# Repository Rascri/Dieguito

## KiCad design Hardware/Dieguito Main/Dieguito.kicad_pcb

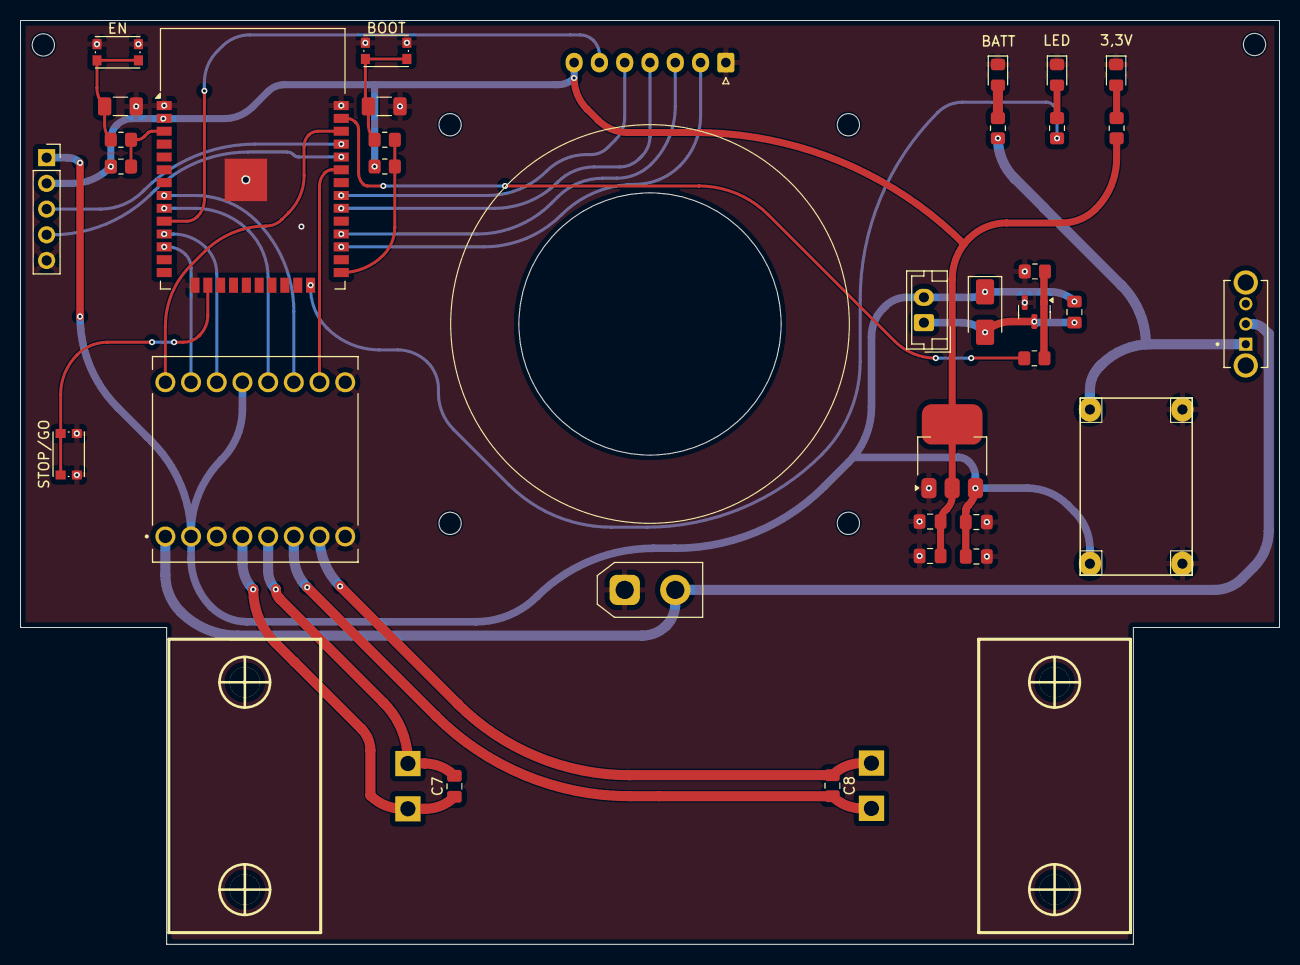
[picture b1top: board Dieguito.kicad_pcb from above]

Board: 2 copper layers, 124.4 x 91.3 mm, 41 parts (1 on the bottom side), 34 nets.

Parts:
3,3V: POWER; LED_0805_2012Metric_Pad1.15x1.40mm_HandSolder
BATT: POWER; LED_0805_2012Metric_Pad1.15x1.40mm_HandSolder
BOOT: BOOT; SW_Push_1P1T_NO_CK_KMR2
Bracket1, Bracket2: VAL**; Pololu_Micro_Bracket_Wheel_42mm
C1, C4, C7, C8: 100n; C_0805_2012Metric_Pad1.18x1.45mm_HandSolder
C2, C3: 10u; C_0805_2012Metric_Pad1.18x1.45mm_HandSolder
C5, C6: 1n; C_1206_3216Metric_Pad1.33x1.80mm_HandSolder
C9: 0.1uF; C_0805_2012Metric_Pad1.18x1.45mm_HandSolder
D4: SS34; D_SMA
EN: ENABLE; SW_Push_1P1T_NO_CK_KMR2
H1, H2: Mounting_Hole; MountingHole_2.2mm_M2
J1: XT30; AMASS_XT30UPB-M_1x02_P5.0mm_Vertical
J2, J3: Cable_PAD; Cable_3_1,5mm
J4: Programador; PinSocket_1x05_P2.54mm_Vertical
J5: Sensores; JST_XH_S7B-XH-A-1_1x07_P2.50mm_Horizontal
J6: Turbina; JST_EH_B2B-EH-A_1x02_P2.50mm_Vertical
LED: POWER; LED_0805_2012Metric_Pad1.15x1.40mm_HandSolder
Q1: AO3400A; SOT-23
R1, R3, R5: 470; R_0805_2012Metric_Pad1.20x1.40mm_HandSolder
R2, R7: 1k; R_0805_2012Metric_Pad1.20x1.40mm_HandSolder
R4, R6: 10k; R_0805_2012Metric_Pad1.20x1.40mm_HandSolder
R8: 47k; R_0805_2012Metric_Pad1.20x1.40mm_HandSolder
R9: 100; R_0805_2012Metric_Pad1.20x1.40mm_HandSolder
STOP/GO: GO/STOP; SW_Push_1P1T_NO_CK_KMR2
SW4: SW_SPDT; SW_EG1247
U1: ROB-14450; MODULE_ROB-14450
U2: ESP32-WROOM-32
U3: AMS1117-3.3; SOT-223-3_TabPin2
U4: Mini360; Mini360_step-down

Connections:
+3.3V: C3.1, C4.1, J4.2, J5.7, R2.1, R4.2, R6.2, U2.2 (VDD), U3.2 (VO)
+5V: C1.1, C2.1, C9.1, D4.1 (K), J4.1, J6.2, U1.2 (VCC), U1.13 (STBY), U3.3 (VI), U4.3 (OUT)
/VM: J1.2, SW4.2 (B), U1.1 (VM)
AI1: U1.14 (AI1), U2.11 (IO26)
AI2: U1.15 (AI2), U2.12 (IO27)
BI1: U1.12 (BI1), U2.9 (IO33)
BI2: U1.11 (BI2), U2.8 (IO32)
D13: STOP/GO.1, U2.16 (IO13)
D23: R9.2, U2.37 (IO23)
EN: R3.2, R4.1, U2.3 (EN)
GND: 3,3V.1 (K), BATT.1 (K), BOOT.1, C1.2, C2.2, C3.2, C4.2, C5.1, C6.1, EN.1, J1.1, J4.5, J5.1, LED.1 (K), Q1.2 (S), R8.1, STOP/GO.2, U1.3 (GND), U1.8 (GND), U1.9 (GND), U2.1 (GND), U2.15 (GND), U2.38 (GND), U2.39 (GND), U3.1 (GND), U4.2 (GND)
IO0: R5.2, R6.1, U2.25 (IO0)
LED: R1.1, U2.24 (IO2)
M0: J5.5, U2.31 (IO19)
M1: J5.4, U2.30 (IO18)
M2: J5.3, U2.28 (IO17)
M3: J5.2, U2.27 (IO16)
unnamed: C5.2, EN.2, R3.1
unnamed: BOOT.2, C6.2, R5.1
unnamed: LED.2 (A), R1.2
unnamed: 3,3V.2 (A), R2.2
unnamed: BATT.2 (A), R7.2
unnamed: C9.2, D4.2 (A), J6.1, Q1.3 (D)
unnamed: Q1.1 (G), R8.2, R9.1
unnamed: C7.1, J2.2, U1.4 (A01)
unnamed: C7.2, J2.1, U1.5 (A02)
unnamed: C8.1, J3.2, U1.7 (B01)
unnamed: C8.2, J3.1, U1.6 (B02)
PWMA: U1.16 (PWMA), U2.36 (IO22)
PWMB: U1.10 (PWMB), U2.33 (IO21)
RXD0: J4.4, U2.34 (RXD0/IO3)
SIG: J5.6, U2.10 (IO25)
TXD0: J4.3, U2.35 (TXD0/IO1)
VCC: R7.1, SW4.1 (A), U4.1 (IN)

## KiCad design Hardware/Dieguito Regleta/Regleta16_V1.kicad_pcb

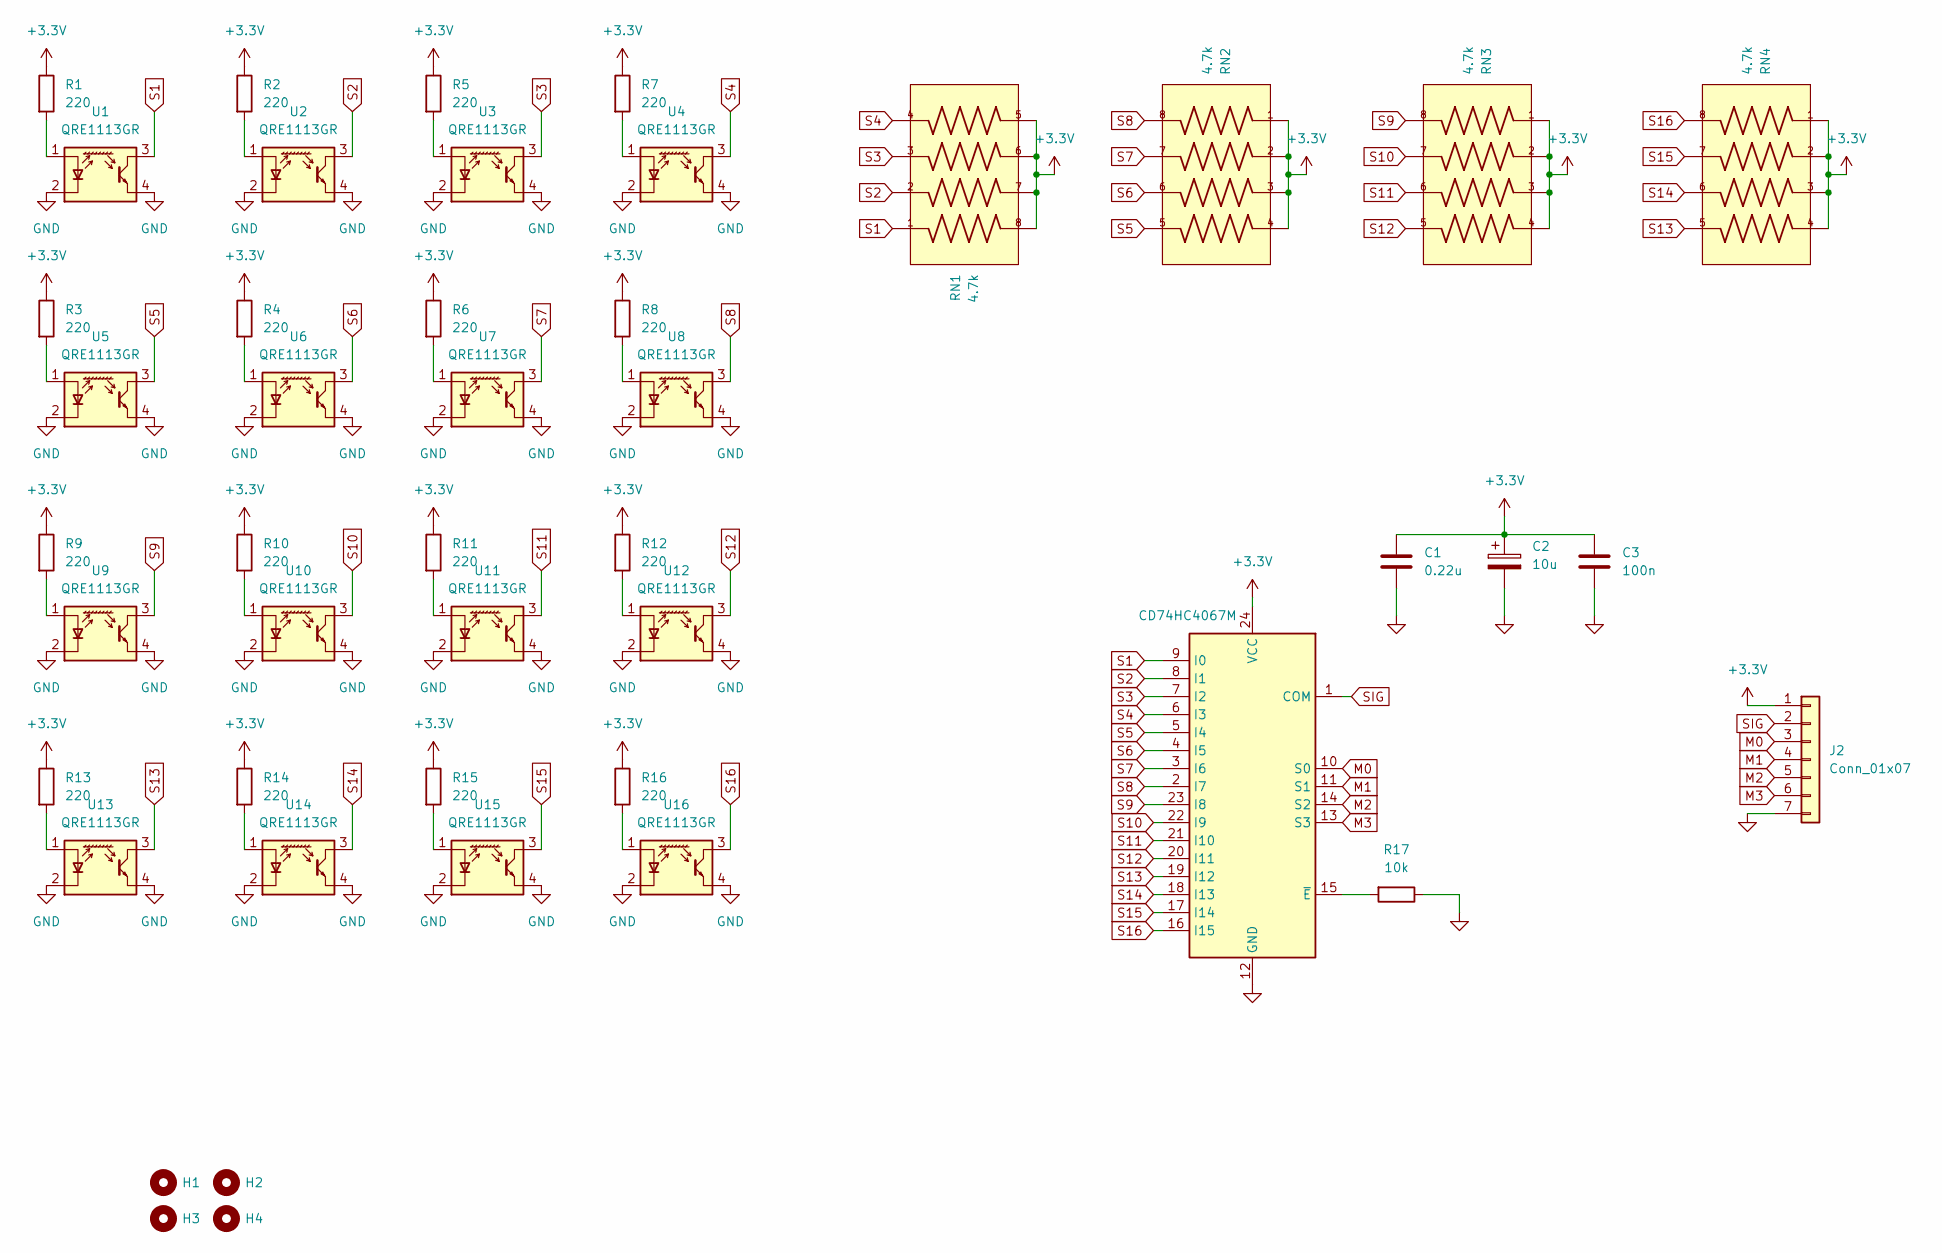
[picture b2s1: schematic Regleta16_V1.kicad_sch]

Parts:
C1: 0.22u; C_0805_2012Metric_Pad1.18x1.45mm_HandSolder
C2: 10u; CP_Elec_4x5.4
C3: 100n; C_0805_2012Metric_Pad1.18x1.45mm_HandSolder
H1, H2, H3, H4: Mounting_Hole; MountingHole_2.2mm_M2
J2: Conn_01x07; JST_XH_S7B-XH-A-1_1x07_P2.50mm_Horizontal
R1, R2, R3, R4, R5, R6, R7, R8, R9, R10, R11, R12, R13, R14, R15, R16: 220; R_0805_2012Metric_Pad1.20x1.40mm_HandSolder
R17: 10k; R_0805_2012Metric_Pad1.20x1.40mm_HandSolder
RN1, RN2, RN3, RN4: 4.7k; R_Array_Convex_4x1206
U1, U2, U3, U4, U5, U6, U7, U8, U9, U10, U11, U12, U13, U14, U15, U16: QRE1113GR; Qre1113_smd_dieguito
U18: CD74HC4067M; SOIC-24W_7.5x15.4mm_P1.27mm

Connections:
+3.3V: C1.1, C2.1, C3.1, J2.1, R1.1, R2.1, R3.1, R4.1, R5.1, R6.1, R7.1, R8.1, R9.1, R10.1, R11.1, R12.1, R13.1, R14.1, R15.1, R16.1, RN1.5, RN1.6, RN1.7, RN1.8, RN2.1, RN2.2, RN2.3, RN2.4, RN3.1, RN3.2, RN3.3, RN3.4, RN4.1, RN4.2, RN4.3, RN4.4, U18.24 (VCC)
GND: C1.2, C2.2, C3.2, J2.7, R17.1, U1.2 (K), U1.4, U2.2 (K), U2.4, U3.2 (K), U3.4, U4.2 (K), U4.4, U5.2 (K), U5.4, U6.2 (K), U6.4, U7.2 (K), U7.4, U8.2 (K), U8.4, U9.2 (K), U9.4, U10.2 (K), U10.4, U11.2 (K), U11.4, U12.2 (K), U12.4, U13.2 (K), U13.4, U14.2 (K), U14.4, U15.2 (K), U15.4, U16.2 (K), U16.4, U18.12 (GND)
M0: J2.3, U18.10 (S0)
M1: J2.4, U18.11 (S1)
M2: J2.5, U18.14 (S2)
M3: J2.6, U18.13 (S3)
unnamed: R1.2, U1.1 (A)
unnamed: R2.2, U2.1 (A)
unnamed: R5.2, U3.1 (A)
unnamed: R7.2, U4.1 (A)
unnamed: R3.2, U5.1 (A)
unnamed: R4.2, U6.1 (A)
unnamed: R6.2, U7.1 (A)
unnamed: R8.2, U8.1 (A)
unnamed: R9.2, U9.1 (A)
unnamed: R10.2, U10.1 (A)
unnamed: R11.2, U11.1 (A)
unnamed: R12.2, U12.1 (A)
unnamed: R13.2, U13.1 (A)
unnamed: R14.2, U14.1 (A)
unnamed: R15.2, U15.1 (A)
unnamed: R16.2, U16.1 (A)
unnamed: R17.2, U18.15 (~E)
S1: RN1.1, U1.3, U18.9 (I0)
S2: RN1.2, U2.3, U18.8 (I1)
S3: RN1.3, U3.3, U18.7 (I2)
S4: RN1.4, U4.3, U18.6 (I3)
S5: RN2.5, U5.3, U18.5 (I4)
S6: RN2.6, U6.3, U18.4 (I5)
S7: RN2.7, U7.3, U18.3 (I6)
S8: RN2.8, U8.3, U18.2 (I7)
S9: RN3.8, U9.3, U18.23 (I8)
S10: RN3.7, U10.3, U18.22 (I9)
S11: RN3.6, U11.3, U18.21 (I10)
S12: RN3.5, U12.3, U18.20 (I11)
S13: RN4.5, U13.3, U18.19 (I12)
S14: RN4.6, U14.3, U18.18 (I13)
S15: RN4.7, U15.3, U18.17 (I14)
S16: RN4.8, U16.3, U18.16 (I15)
SIG: J2.2, U18.1 (COM)

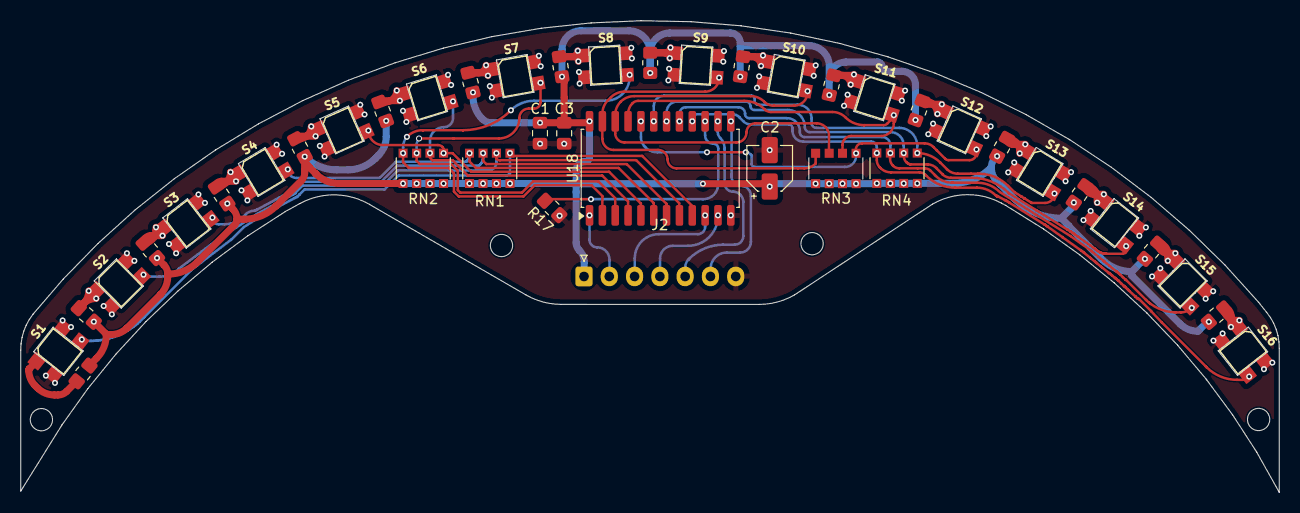
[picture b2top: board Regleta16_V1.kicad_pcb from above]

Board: 2 copper layers, 124.4 x 46.6 mm, 46 parts (0 on the bottom side), 40 nets.

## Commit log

2025-10-03 Primer commit
2025-10-03 Subo carpetas
2025-10-03 Actualizo Hardware
2025-10-03 Actualizo carpetas
2025-10-03 Correcion de placa
2025-10-03 Corrijo placa main
